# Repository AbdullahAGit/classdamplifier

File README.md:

Class D Amplifier meant for a speaker and connected to an Arduino Mega

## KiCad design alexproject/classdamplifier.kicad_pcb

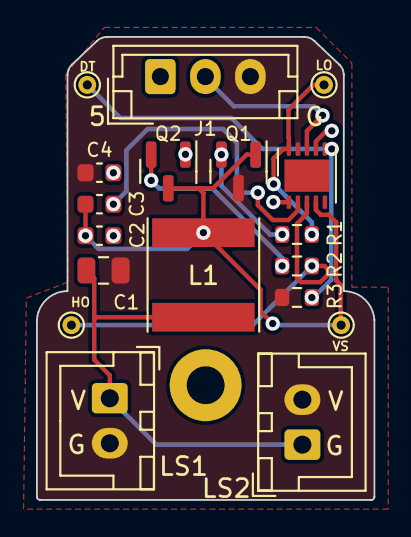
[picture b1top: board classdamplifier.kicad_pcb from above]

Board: 2 copper layers, 18.8 x 25.7 mm, 18 parts (0 on the bottom side), 11 nets.

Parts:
C1: 1uF; C_0805_2012Metric
C2: 1000pF; C_0603_1608Metric
C3: 100n; C_0603_1608Metric
C4: 7pF; C_0603_1608Metric
DGD5463: DGD05463; WDFN-10-1EP_3x3mm_P0.5mm_EP1.8x2.5mm
DT: TestPoint; TestPoint_THTPad_D1.0mm_Drill0.5mm
HO: TestPoint; TestPoint_THTPad_D1.0mm_Drill0.5mm
J1: Conn_01x03_Pin; JST_EH_B3B-EH-A_1x03_P2.50mm_Vertical
L1: 63.7uH; L_Taiyo-Yuden_NR-60xx
LO: TestPoint; TestPoint_THTPad_D1.0mm_Drill0.5mm
LS1, LS2: Speaker; JST_XH_B2B-XH-A_1x02_P2.50mm_Vertical
Q1, Q2: NMOS; SOT-23
R1, R2: 10; R_0603_1608Metric
R3: 10k; R_0603_1608Metric
VS: TestPoint; TestPoint_THTPad_D1.0mm_Drill0.5mm

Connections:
+5V: C2.1, C4.1, DGD5463.1 (VCC), DGD5463.7 (EN), J1.1, Q2.1 (D)
GND: C1.2, C4.2, DGD5463.9 (COM), J1.3, LS1.2, LS2.2, Q1.3 (S), R3.1
IN: DGD5463.8 (IN), J1.2
unnamed: C1.1, L1.2, LS1.1, LS2.1
unnamed: DGD5463.6 (DT), DT.1, R3.2
unnamed: DGD5463.3 (HO), HO.1, R2.2
unnamed: DGD5463.10 (LO), LO.1, R1.2
unnamed: C3.1, DGD5463.2 (VB)
unnamed: C2.2, C3.2, DGD5463.4 (VS), L1.1, Q1.1 (D), Q2.3 (S), VS.1
unnamed: Q1.2 (G), R1.1
unnamed: Q2.2 (G), R2.1

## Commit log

2024-06-13 testing spice sim & updated PCB
2024-06-24 updated silkscreen
